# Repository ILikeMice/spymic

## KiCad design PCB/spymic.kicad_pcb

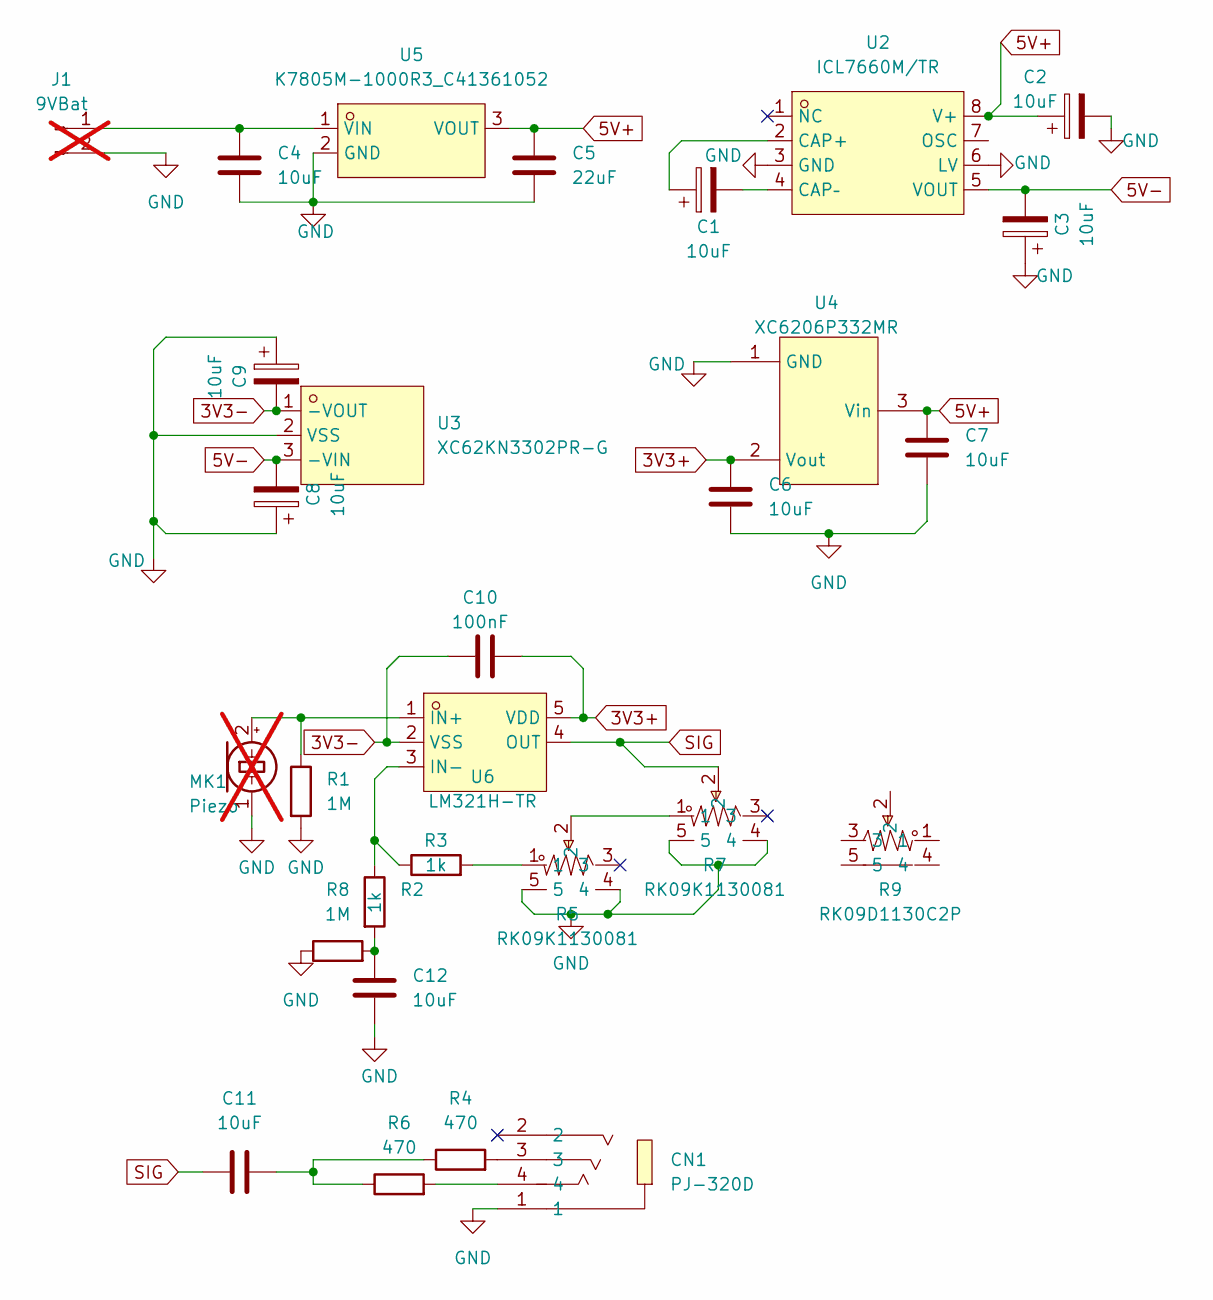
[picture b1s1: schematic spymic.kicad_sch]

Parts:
C1, C2, C3, C8, C9: 10uF; CP_Elec_4x5.4; LCSC Part C72485
C4, C6, C7, C11, C12: 10uF; C_0603_1608Metric_Pad1.08x0.95mm_HandSolder; LCSC Part C1691
C5: 22uF; C_0603_1608Metric_Pad1.08x0.95mm_HandSolder; LCSC Part C59461
C10: 100nF; C_0603_1608Metric_Pad1.08x0.95mm_HandSolder; LCSC Part C59461
CN1: PJ-320D; AUDIO-SMD_PJ-320D-1; LCSC Part C431535
J1: 9VBat; SolderWire-0.25sqmm_1x02_P4.5mm_D0.65mm_OD2mm_Relief; not fitted
MK1: Piezo; SolderWire-0.25sqmm_1x02_P4.5mm_D0.65mm_OD2mm_Relief; not fitted
R1, R8: 1M; R_1206_3216Metric_Pad1.30x1.75mm_HandSolder; LCSC Part C17927
R2, R3: 1k; R_0603_1608Metric_Pad0.98x0.95mm_HandSolder; LCSC Part C2907002
R4, R6: 470; R_0603_1608Metric_Pad0.98x0.95mm_HandSolder; LCSC Part C23179
R5, R7: RK09K1130081; RES-TH_RK09K1130AAU; MPN RK09K1130081; LCSC Part C470311
R9: RK09D1130C2P; RES-TH_RK09D1130C2P; MPN RK09D1130C2P; LCSC Part C361173
U2: ICL7660M/TR; SOP-8_L4.9-W3.9-P1.27-LS6.0-BL; MPN ICL7660M/TR; LCSC Part C356724
U3: XC62KN3302PR-G; SOT-89-3_L4.5-W2.5-P1.50-LS4.2-BR; MPN XC62KN3302PR-G; LCSC Part C165901
U4: XC6206P332MR; SOT-23-3_L2.9-W1.6-P1.90-LS2.8-BR; MPN XC6206P332MR-G; LCSC Part C5446
U5: K7805M-1000R3_C41361052; PWRM-TH_DEXU_K780XM-1000R3; MPN K7805M-1000R3; LCSC Part C41361052
U6: LM321H-TR; SOT-23-5_L2.9-W1.6-P0.95-LS2.8-BL; MPN LM321H-TR; LCSC Part C2927688

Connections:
3V3+: C6.1, C10.2, U4.2 (Vout), U6.5 (VDD)
3V3-: C9.2, C10.1, U3.1 (-VOUT), U6.2 (VSS)
5V+: C2.1, C5.1, C7.1, U2.8 (V+), U4.3 (Vin), U5.3 (VOUT)
5V-: C3.2, C8.2, U2.5 (VOUT), U3.3 (-VIN)
GND: C2.2, C3.1, C4.2, C5.2, C6.2, C7.2, C8.1, C9.1, C12.2, CN1.1, J1.2, MK1.1 (-), R1.2, R5.4, R5.5, R7.4, R7.5, R8.1, U2.3 (GND), U2.6 (LV), U3.2 (VSS), U4.1 (GND), U5.2 (GND)
unnamed: C11.2, R4.1, R6.1
unnamed: C12.1, R2.2, R8.2
unnamed: CN1.3, R4.2
unnamed: CN1.4, R6.2
unnamed: C4.1, J1.1, U5.1 (VIN)
unnamed: MK1.2 (+), R1.1, U6.1 (IN+)
unnamed: R3.2, R5.1
unnamed: R5.2, R7.1
unnamed: C1.1, U2.2 (CAP+)
unnamed: C1.2, U2.4 (CAP–)
unnamed: R2.1, R3.1, U6.3 (IN-)
SIG: C11.1, R7.2, U6.4 (OUT)

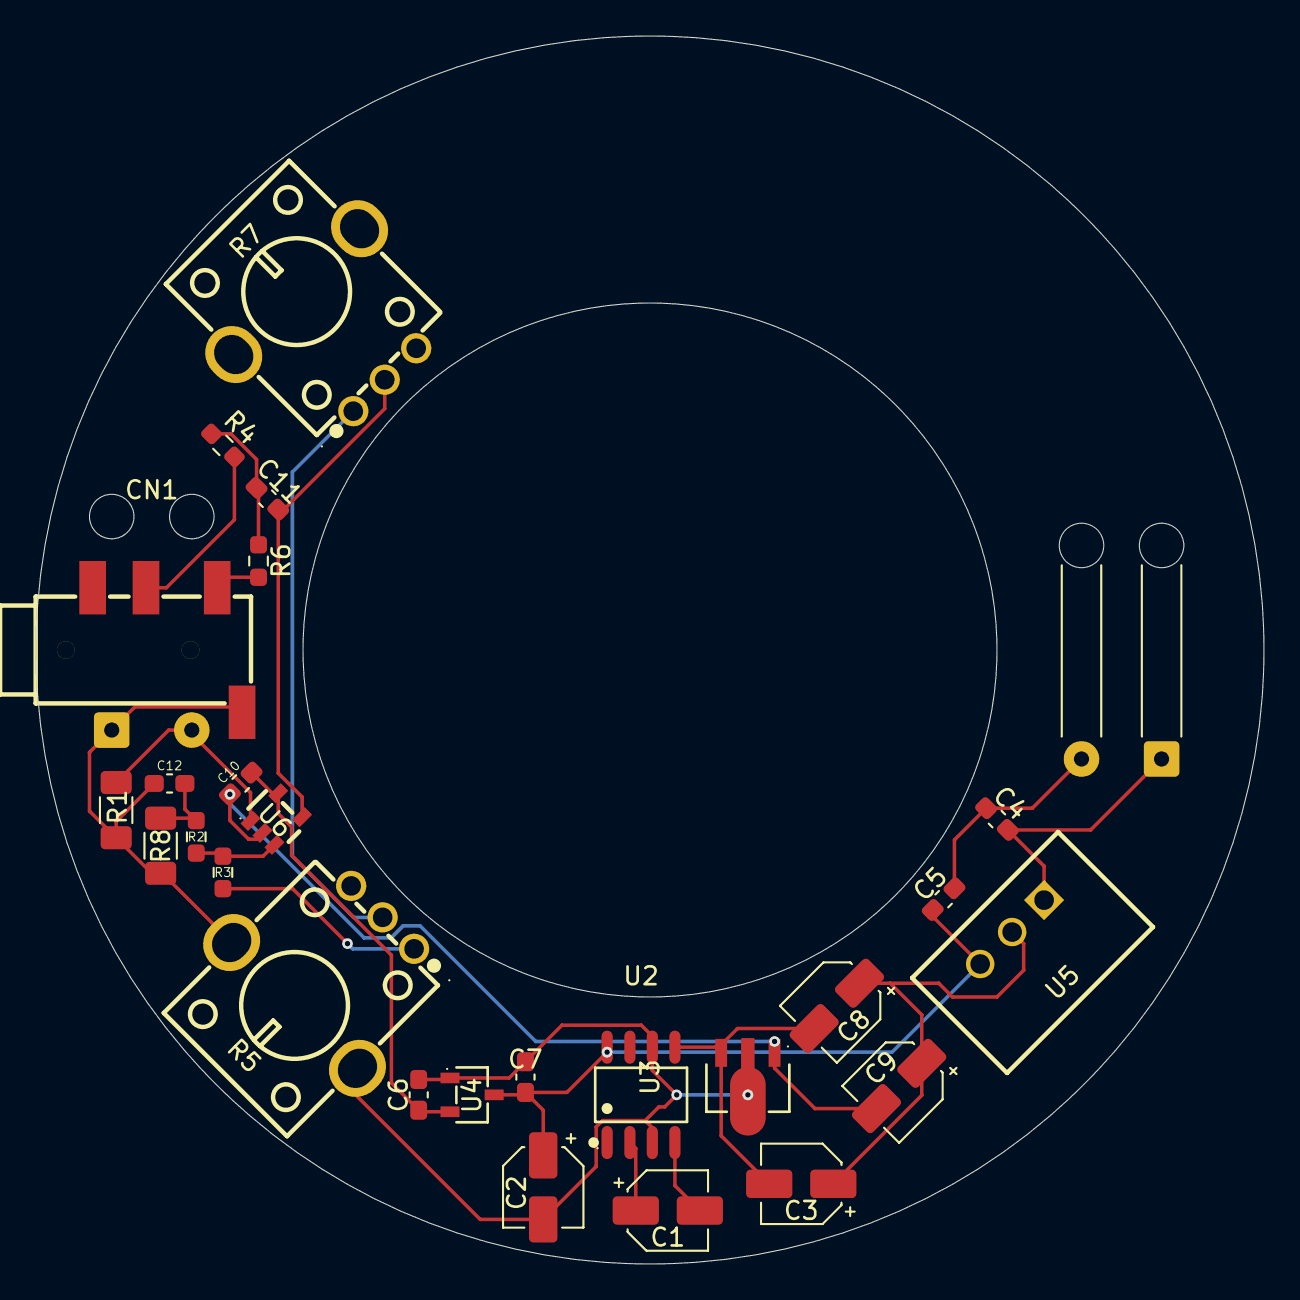
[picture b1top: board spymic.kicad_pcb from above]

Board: 2 copper layers, 69.0 x 69.0 mm, 28 parts (1 on the bottom side), 17 nets.

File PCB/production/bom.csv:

Designator,Footprint,Quantity,Value,LCSC Part #
"C1, C2, C3, C8, C9",CP_Elec_4x5.4,5,10uF,C72485
C10,0603,1,100nF,C59461
"C11, C12, C4, C6, C7",0603,5,10uF,C1691
C5,0603,1,22uF,C59461
CN1,AUDIO-SMD_PJ-320D-1,1,PJ-320D,C431535
"R1, R8",1206,2,1M,C17927
"R2, R3",0603,2,1k,C2907002
"R4, R6",0603,2,470,C23179
"R5, R7",RES-TH_RK09K1130AAU,2,RK09K1130081,C470311
U2,SOP-8_L4.9-W3.9-P1.27-LS6.0-BL,1,ICL7660M/TR,C356724
U3,SOT-89-3_L4.5-W2.5-P1.50-LS4.2-BR,1,XC62KN3302PR-G,C165901
U4,SOT-23-3_L2.9-W1.6-P1.90-LS2.8-BR,1,XC6206P332MR,C5446
U5,PWRM-TH_DEXU_K780XM-1000R3,1,K7805M-1000R3_C41361052,C41361052
U6,SOT-23-5_L2.9-W1.6-P0.95-LS2.8-BL,1,LM321H-TR,C2927688
